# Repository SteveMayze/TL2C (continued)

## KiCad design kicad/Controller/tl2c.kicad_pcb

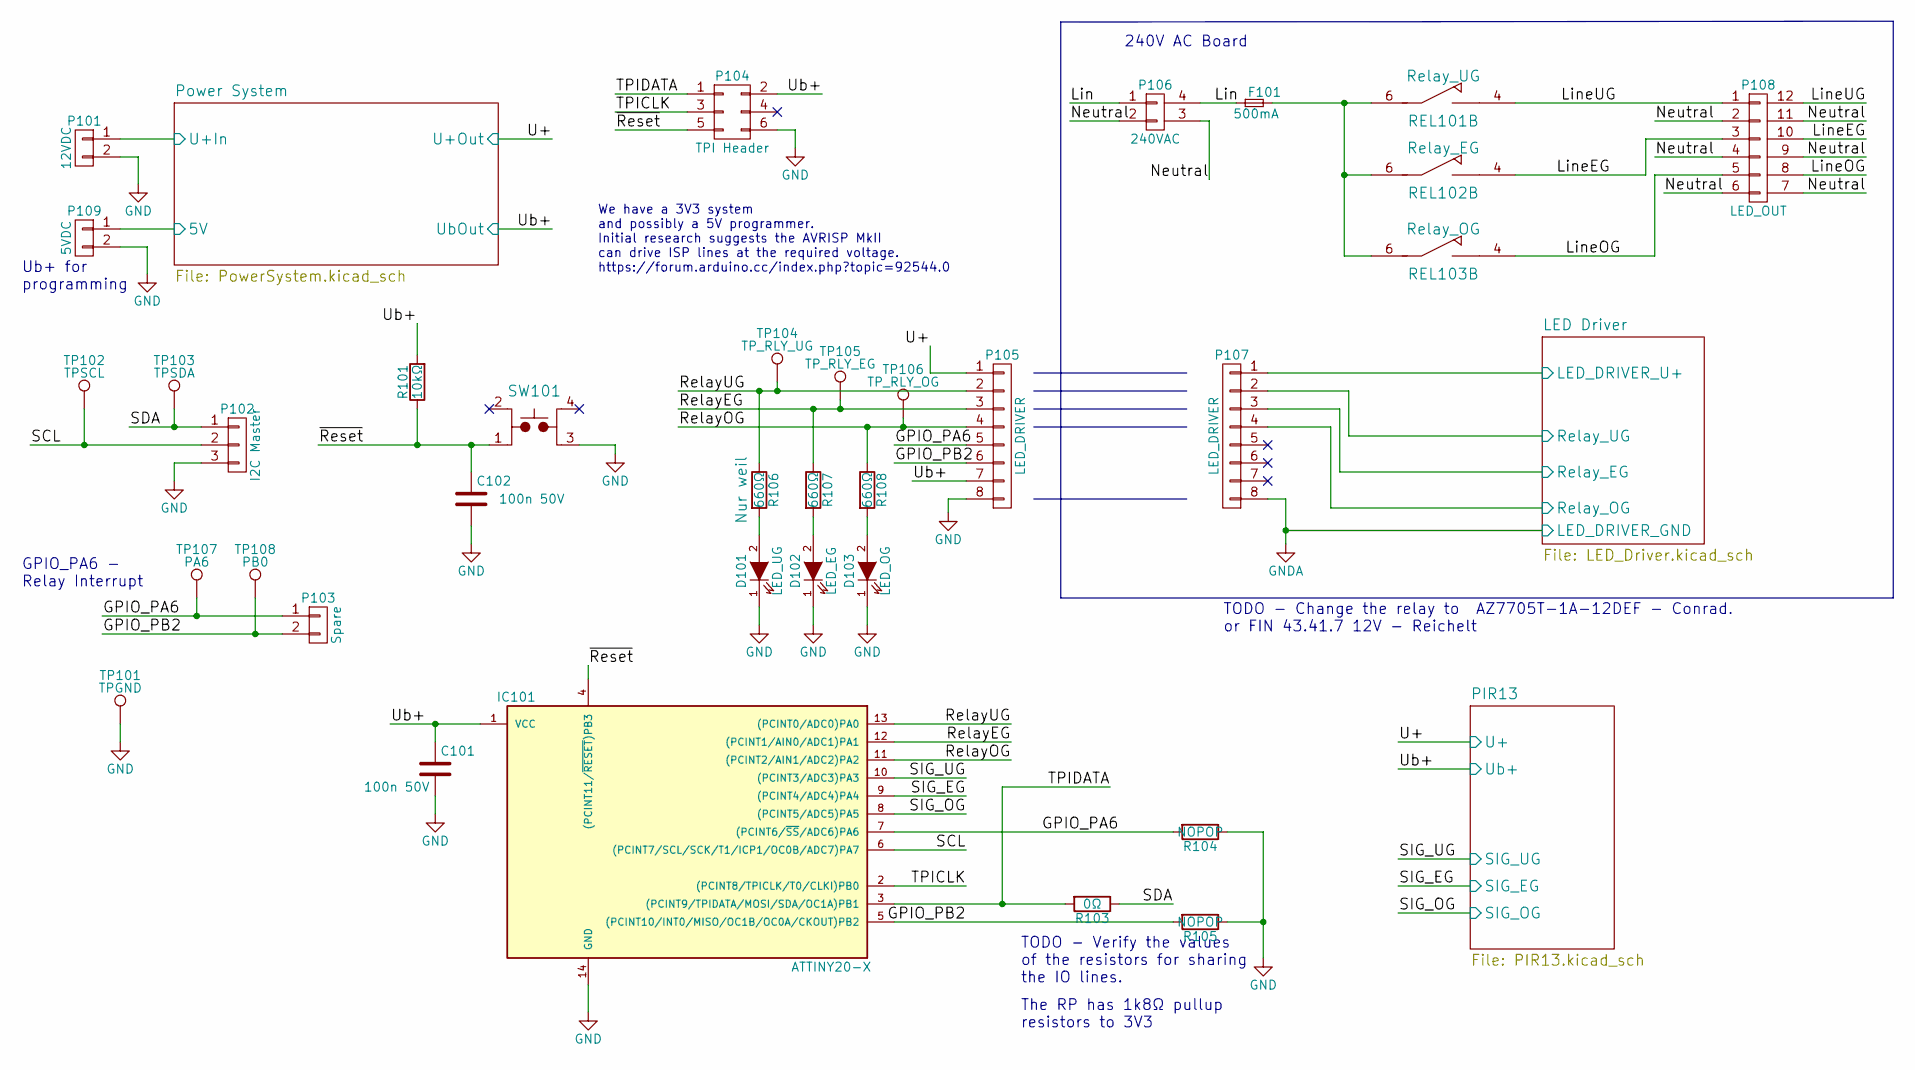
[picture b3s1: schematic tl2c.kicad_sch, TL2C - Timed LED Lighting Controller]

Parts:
C101, C102: 100n 50V; C_0805
D101: LED_UG; LED_0805
D102: LED_EG; LED_0805
D103: LED_OG; LED_0805
F101: 500mA; Fuse_TE5_Littlefuse-ESKA_887_O14; Digikey-PN Value
IC101: ATTINY20-X; SOIC-14_3.9x8.7mm_Pitch1.27mm; Digikey-PN ATTINY20-SSURCT-ND
P101: 12VDC; Pin_Header_Straight_1x02; Digikey-PN Value
P102: I2C Master; Spring_Terminal_Block_1_x_3; Digikey-PN Value
P103: Spare; Pin_Header_Straight_1x02; Digikey-PN Value
P104: TPI Header; TC2030-IDC-FP_ISP_Connector; Digikey-PN Value
P105, P107: LED_DRIVER; Pin_Header_Straight_1x08_Pitch2.54mm; Digikey-PN Value
P106: 240VAC; Spring_Terminal_Block_1_x_2_5mm; Digikey-PN Value
P108: LED_OUT; Spring_Terminal_Block_1_x_6_5mm; Digikey-PN Value
P109: 5VDC; Pin_Header_Straight_1x02_Pitch2.54mm; Digikey-PN Value
R101: 10kΩ; R_0805
R103: 0Ω; R_0805
R104, R105: NOPOP; R_0805
R106, R107, R108: 660Ω; R_0805
REL101: Relay_UG; JW1AFSN-12-F; Digikey-PN Value
REL102: Relay_EG; JW1AFSN-12-F; Digikey-PN Value
REL103: Relay_OG; JW1AFSN-12-F; Digikey-PN Value
SW101: TL3315NF160Q; PTS525SM15SMTR2LFS; Digikey-PN Value
TP101: TPGND; Measurement_Point_Round-SMD-Pad_Small
TP102: TPSCL; Measurement_Point_Round-SMD-Pad_Small
TP103: TPSDA; Measurement_Point_Round-SMD-Pad_Small
TP104: TP_RLY_UG; Measurement_Point_Round-SMD-Pad_Small
TP105: TP_RLY_EG; Measurement_Point_Round-SMD-Pad_Small
TP106: TP_RLY_OG; Measurement_Point_Round-SMD-Pad_Small
TP107: PA6; Measurement_Point_Round-SMD-Pad_Small
TP108: PB0; Measurement_Point_Round-SMD-Pad_Small

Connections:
/GPIO_PA6: IC101.7 ((PCINT6/~SS/ADC6)PA6), P103.1, P105.5, R104.2, TP107.1
/GPIO_PB2: IC101.5 ((PCINT10/INT0/MISO/OC1B/OC0A/CKOUT)PB2), P103.2, P105.6, R105.2, TP108.1
/LED Driver/LED_DRIVER_U+: P107.1; also elsewhere on the board
/LED Driver/Relay_EG: P107.3; also elsewhere on the board
/LED Driver/Relay_OG: P107.4; also elsewhere on the board
/LED Driver/Relay_UG: P107.2; also elsewhere on the board
/Lin: F101.1, P106.1, P106.4
/LineEG: P108.3, P108.10, REL102.4
/LineOG: P108.5, P108.8, REL103.4
/LineUG: P108.1, P108.12, REL101.4
/Neutral: P106.2, P106.3, P108.2, P108.4, P108.6, P108.7, P108.9, P108.11
/PIR13/SIG_EG: IC101.9 ((PCINT4/ADC4)PA4); also elsewhere on the board
/PIR13/SIG_OG: IC101.8 ((PCINT5/ADC5)PA5); also elsewhere on the board
/PIR13/SIG_UG: IC101.10 ((PCINT3/ADC3)PA3); also elsewhere on the board
/PIR13/U+: P105.1; also elsewhere on the board
/PIR13/Ub+: C101.1, IC101.1 (VCC), P104.2, P105.7, R101.2; also elsewhere on the board
/Power System/5V: P109.1; also elsewhere on the board
/Power System/U+In: P101.1; also elsewhere on the board
/RelayEG: IC101.12 ((PCINT1/AIN0/ADC1)PA1), P105.3, R107.1, TP105.1
/RelayOG: IC101.11 ((PCINT2/AIN1/ADC2)PA2), P105.4, R108.1, TP106.1
/RelayUG: IC101.13 ((PCINT0/ADC0)PA0), P105.2, R106.1, TP104.1
/SCL: IC101.6 ((PCINT7/SCL/SCK/T1/ICP1/OC0B/ADC7)PA7), P102.2, TP102.1
/SDA: P102.1, R103.1, TP103.1
/TPICLK: IC101.2 ((PCINT8/TPICLK/T0/CLKI)PB0), P104.3
/TPIDATA: IC101.3 ((PCINT9/TPIDATA/MOSI/SDA/OC1A)PB1), P104.1, R103.2
/~Reset: C102.1, IC101.4 ((PCINT11/~RESET)PB3), P104.5, R101.1, SW101.1
GND: C101.2, C102.2, D101.1 (K), D102.1 (K), D103.1 (K), IC101.14 (GND), P101.2, P102.3, P104.6, P105.8, P109.2, R104.1, R105.1, SW101.3, TP101.1; also elsewhere on the board
GNDA: P107.8; also elsewhere on the board
unnamed: D101.2 (A), R106.2
unnamed: D102.2 (A), R107.2
unnamed: D103.2 (A), R108.2
unnamed: F101.2, REL101.6, REL102.6, REL103.6

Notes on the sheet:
TODO - Verify the values of the resistors for sharing the IO lines.
TODO - Change the relay to AZ7705T-1A-12DEF - Conrad. or FIN 43.41.7 12V - Reichelt
The RP has 1k8Ω pullup resistors to 3V3
GPIO_PA6 - Relay Interrupt
We have a 3V3 system and possibly a 5V programmer. Initial research suggests the AVRISP MkII can drive ISP lines at the required voltage. https://forum.arduino.cc/index.php?topic=92544.0
Ub+ for programming
240V AC Board

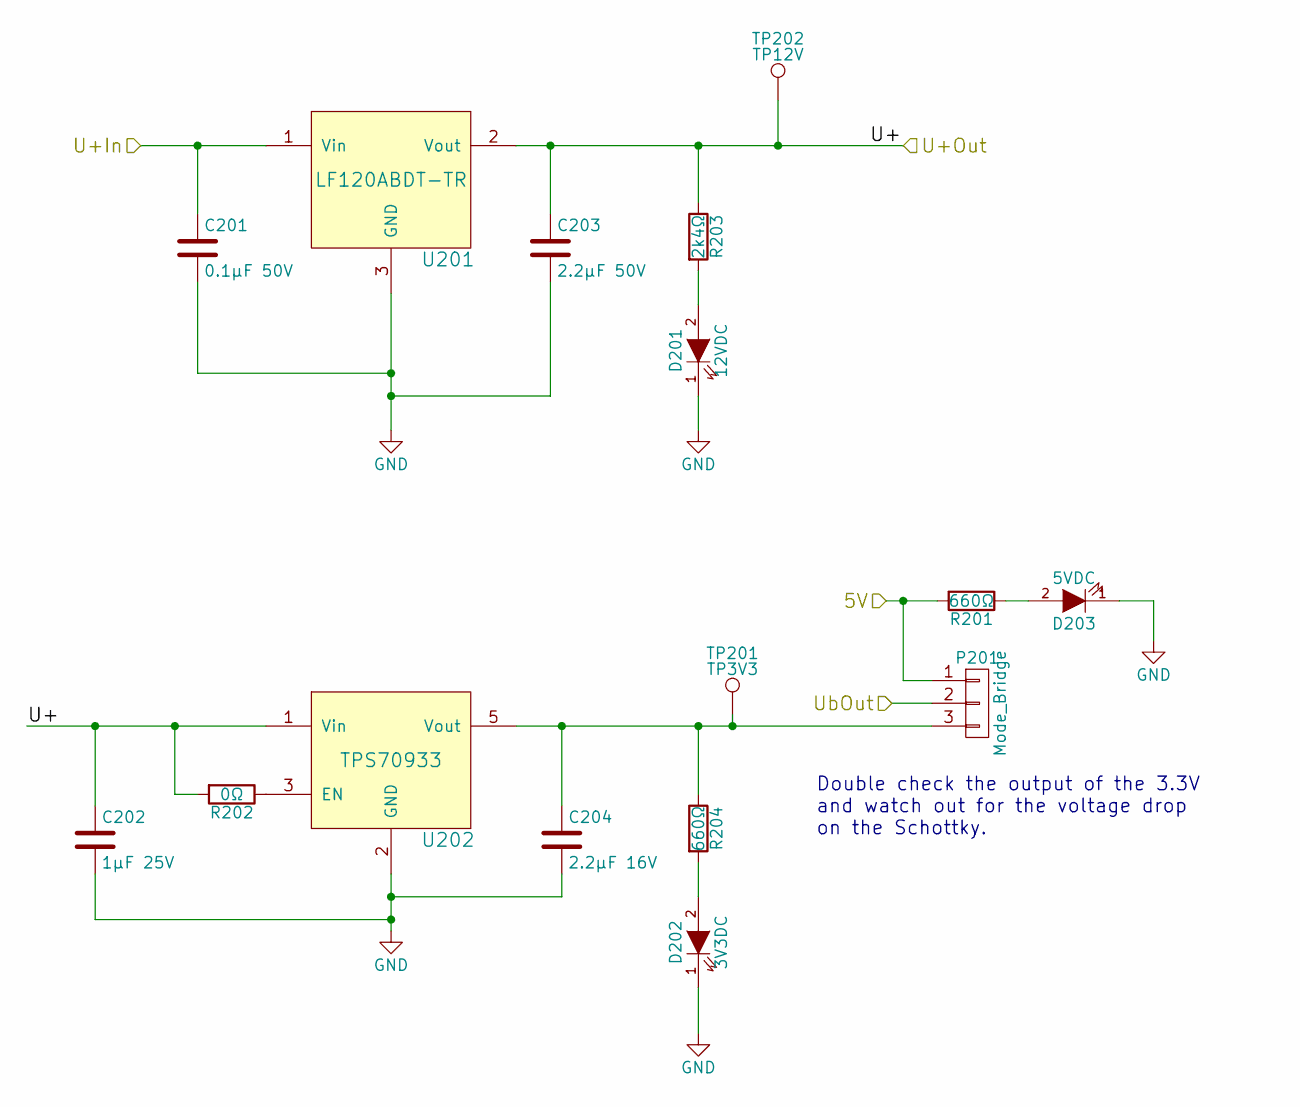
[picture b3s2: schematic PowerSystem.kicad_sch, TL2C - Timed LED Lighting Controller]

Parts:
C201: 0.1μF 50V; C_0805
C202: 1μF 25V; C_1210; Digikey-PN Value
C203: 2.2μF 50V; C_1206; Digikey-PN N/A
C204: 2.2μF 16V; C_1210; Digikey-PN Value
D201: 12VDC; LED_0805
D202: 3V3DC; LED_0805
D203: 5VDC; LED_0805
P201: Mode_Bridge; Pin_Header_Straight_1x03_Pitch2.54mm
R201, R204: 660Ω; R_0805
R202: 0Ω; R_0805
R203: 2k4Ω; R_0805
TP201: TP3V3; Measurement_Point_Round-SMD-Pad_Small
TP202: TP12V; Pin_Header_Straight_1x01; Digikey-PN Value
U201: LF120ABDT-TR; Digikey-PN 497-8330-1-ND
U202: TPS70933; TPS70933DBVR; Digikey-PN 296-35483-1-ND

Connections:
/PIR13/U+: C202.1, C203.1, R202.2, R203.1, TP202.1, U201.2 (Vout), U202.1 (Vin); also elsewhere on the board
/PIR13/Ub+: P201.2; also elsewhere on the board
/Power System/5V: P201.1, R201.2; also elsewhere on the board
/Power System/U+In: C201.1, U201.1 (Vin); also elsewhere on the board
GND: C201.2, C202.2, C203.2, C204.2, D201.1 (K), D202.1 (K), D203.1 (K), U201.3 (GND), U202.2 (GND); also elsewhere on the board
unnamed: C204.1, P201.3, R204.1, TP201.1, U202.5 (Vout)
unnamed: D201.2 (A), R203.2
unnamed: D202.2 (A), R204.2
unnamed: D203.2 (A), R201.1
unnamed: R202.1, U202.3 (EN)

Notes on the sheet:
Double check the output of the 3.3V and watch out for the voltage drop on the Schottky.

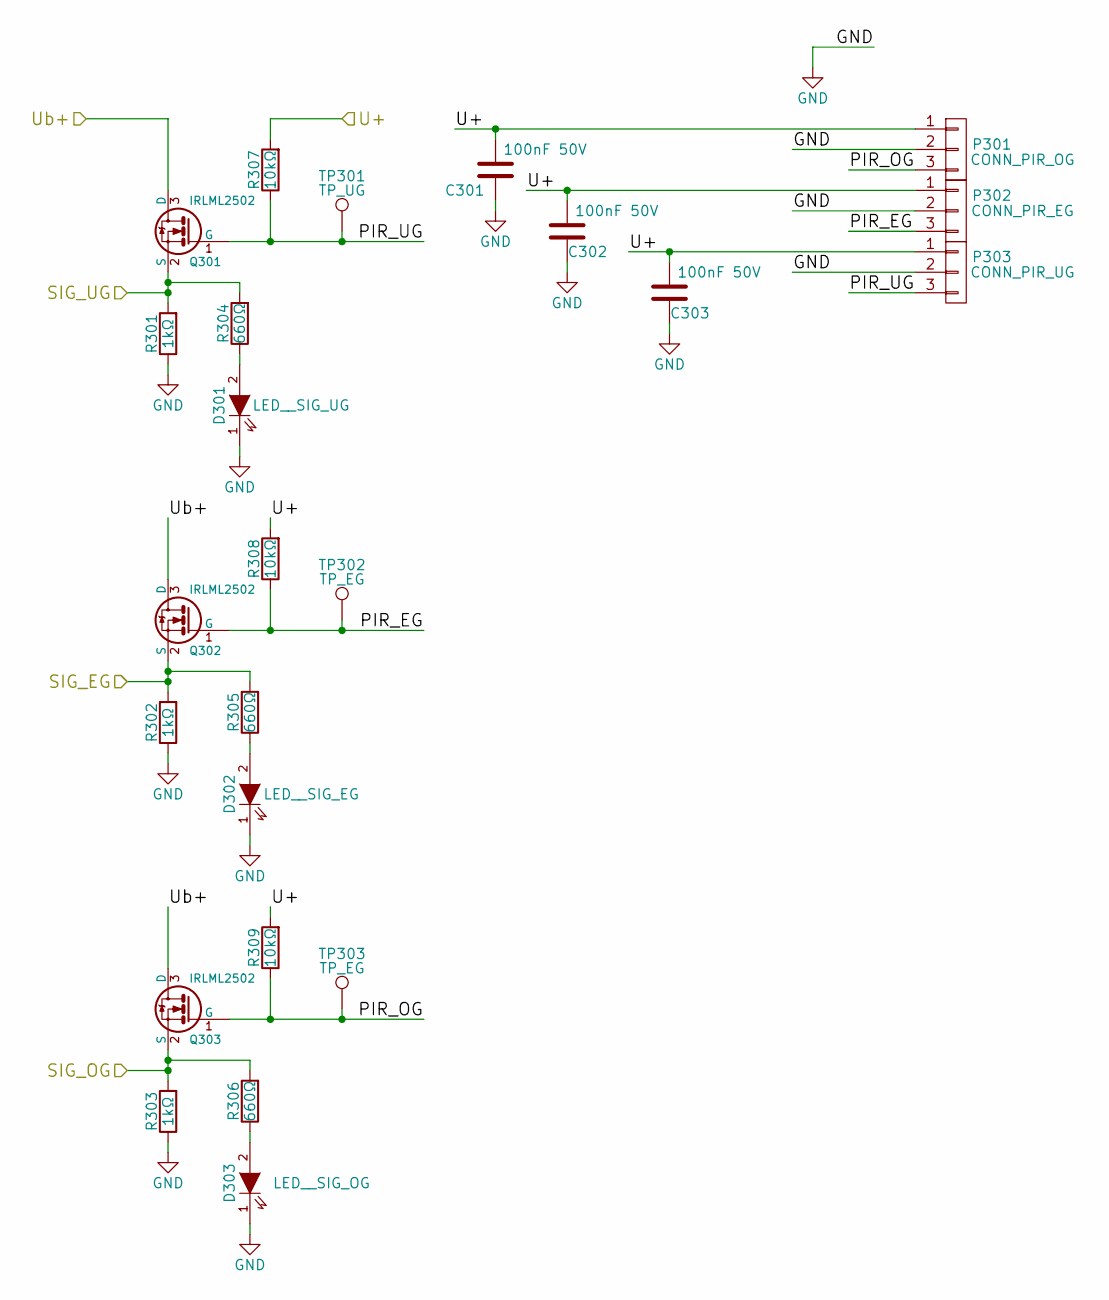
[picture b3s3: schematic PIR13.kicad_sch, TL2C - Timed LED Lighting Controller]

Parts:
C301, C302, C303: 100nF 50V; C_0805
D301: LED__SIG_UG; LED_0805
D302: LED__SIG_EG; LED_0805
D303: LED__SIG_OG; LED_0805
P301: CONN_PIR_OG; Spring_Terminal_Block_1_x_3; Digikey-PN Value
P302: CONN_PIR_EG; Spring_Terminal_Block_1_x_3; Digikey-PN Value
P303: CONN_PIR_UG; Spring_Terminal_Block_1_x_3; Digikey-PN Value
Q301, Q302, Q303: IRLML2502; SOT-23; Digikey-PN IRLML2502GTRPBFCT-ND
R301, R302, R303: 1kΩ; R_0805
R304, R305, R306: 660Ω; R_0805
R307, R308, R309: 10kΩ; R_0805
TP301: TP_UG; Measurement_Point_Round-SMD-Pad_Small
TP302, TP303: TP_EG; Measurement_Point_Round-SMD-Pad_Small

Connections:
/PIR13/PIR_EG: P302.3, Q302.1 (G), R308.1, TP302.1
/PIR13/PIR_OG: P301.3, Q303.1 (G), R309.1, TP303.1
/PIR13/PIR_UG: P303.3, Q301.1 (G), R307.1, TP301.1
/PIR13/SIG_EG: Q302.2 (S), R302.2, R305.2; also elsewhere on the board
/PIR13/SIG_OG: Q303.2 (S), R303.2, R306.2; also elsewhere on the board
/PIR13/SIG_UG: Q301.2 (S), R301.2, R304.2; also elsewhere on the board
/PIR13/U+: C301.2, C302.2, C303.2, P301.1, P302.1, P303.1, R307.2, R308.2, R309.2; also elsewhere on the board
/PIR13/Ub+: Q301.3 (D), Q302.3 (D), Q303.3 (D); also elsewhere on the board
GND: C301.1, C302.1, C303.1, D301.1 (K), D302.1 (K), D303.1 (K), P301.2, P302.2, P303.2, R301.1, R302.1, R303.1; also elsewhere on the board
unnamed: D301.2 (A), R304.1
unnamed: D302.2 (A), R305.1
unnamed: D303.2 (A), R306.1

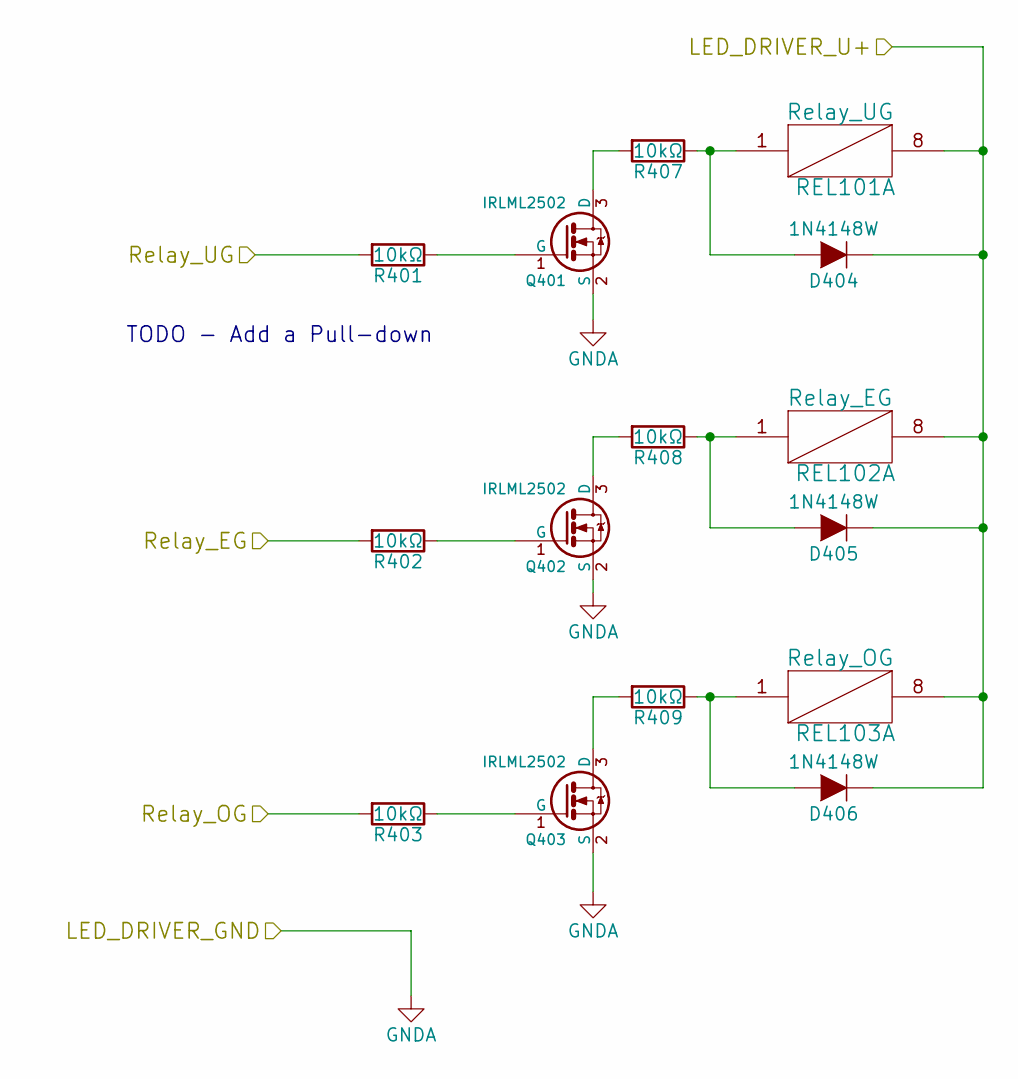
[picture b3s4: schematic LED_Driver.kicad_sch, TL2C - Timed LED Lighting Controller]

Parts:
D404, D405, D406: 1N4148W; SOD-123; Digikey-PN 1N4148W-E3-18CT-ND
Q401: IRLML2502; SOT-23; Digikey-PN IRLML2502GTRPBFCT-ND
Q402, Q403: IRLML2502; SOT-23; Digikey-PN RLML2502GTRPBFCT-ND
R401, R402, R403, R407, R408, R409: 10kΩ; R_0805
REL101: Relay_UG; JW1AFSN-12-F; Digikey-PN N/A
REL102: Relay_EG; JW1AFSN-12-F; Digikey-PN N/A
REL103: Relay_OG; JW1AFSN-12-F; Digikey-PN N/A

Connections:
/LED Driver/LED_DRIVER_U+: D404.1 (K), D405.1 (K), D406.1 (K), REL101.8, REL102.8, REL103.8; also elsewhere on the board
/LED Driver/Relay_EG: R402.2; also elsewhere on the board
/LED Driver/Relay_OG: R403.2; also elsewhere on the board
/LED Driver/Relay_UG: R401.2; also elsewhere on the board
GNDA: Q401.2 (S), Q402.2 (S), Q403.2 (S); also elsewhere on the board
unnamed: D404.2 (A), R407.1, REL101.1
unnamed: D405.2 (A), R408.1, REL102.1
unnamed: D406.2 (A), R409.1, REL103.1
unnamed: Q401.1 (G), R401.1
unnamed: Q401.3 (D), R407.2
unnamed: Q402.1 (G), R402.1
unnamed: Q402.3 (D), R408.2
unnamed: Q403.1 (G), R403.1
unnamed: Q403.3 (D), R409.2

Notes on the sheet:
TODO - Add a Pull-down

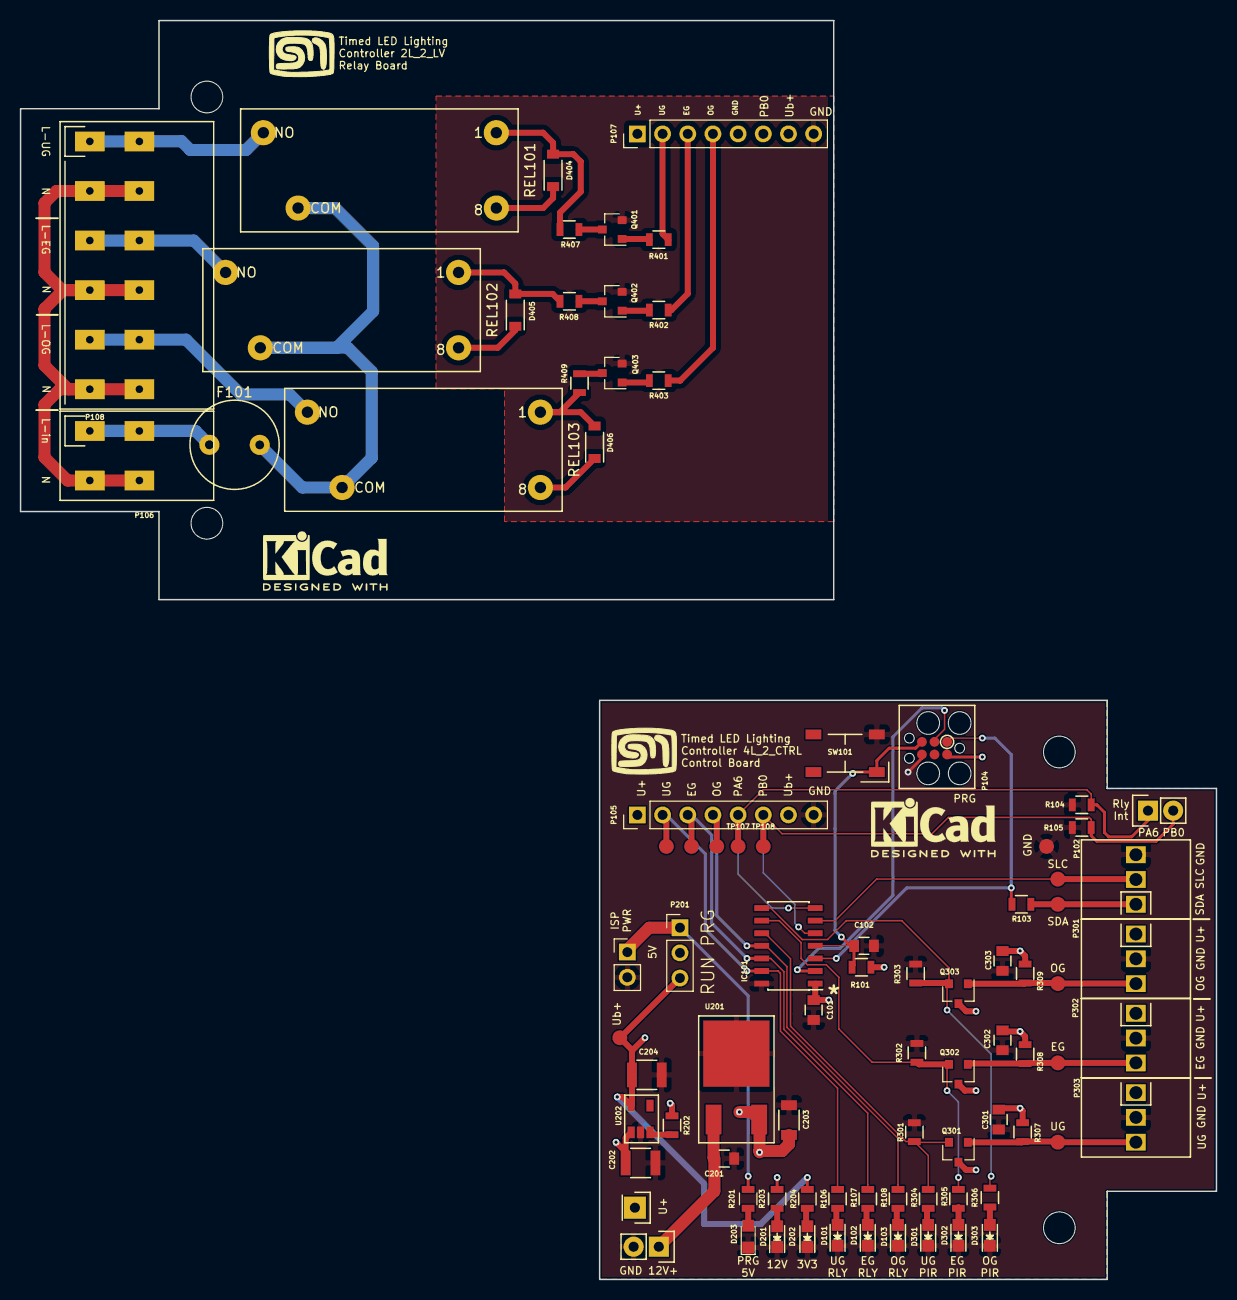
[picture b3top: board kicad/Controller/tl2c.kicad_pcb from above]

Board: 4 copper layers, 120.7 x 127.0 mm, 87 parts (0 on the bottom side), 52 nets.

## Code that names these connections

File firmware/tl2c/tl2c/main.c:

/*
 * tl2c.c
 *
 * Created: 18/02/2017 15:26:52
 * Author : Steve
 */ 

#include <avr/io.h>
#include <avr/interrupt.h>
#include "common.h"
#include "TWI_slave.h"


// volatile unsigned char TL2C_pir_interrupt;
volatile unsigned char timer_delay = 0;
volatile union TL2C_status_reg_t TL2C_pir_state;
unsigned char interrupt_flag;

int main(void)
{
    /* Replace with your application code */

	// Outputs
	// PA0 - UG Untergeschoss relay
	// PA1 - EG	Erdgeschoss relay
	// PA2 - OG	Obergeschoss relay

	// Inputs 
	// PA3 - UG Untergeschoss PIR signal
	// PA4 - EG Erdgeschoss PIR signal
	// PA5 - OG Obergeschoss PIR signal

	// Interrupt (Driver)
	// PA6 - General purpose interrupt output


#define CTC1_MODE	// Testing the timers and interrupts

// The the data direction for the relay outputs
DDRA = 0;
DDRA |= ( 1 << PORTA0 ) | ( 1 << PORTA1 ) | ( 1 << PORTA2 ) | (1 << PORTA6);
PUEA = 0;
PUEA |= ( 1 << PUEA5) | ( 1 << PUEA4) | ( 1 << PUEA3);
// Set the Pin Change interrupts for
PCMSK0 |=   (1<<PCINT5)| (1<<PCINT4)| (1<<PCINT3); // 0b00111000;
GIMSK |= ( 1<<PCIE0 );

#ifdef CTC1_MODE
	// This is the CTC mode whereby the counter registers are are set and a
	// Wave Generator is created. In this example only the OCR0A is used, It
	// is possible also to configure the OCR0B as well.
	// unsigned int startValue = 0x03D0;
	TCCR1A  = 0;										// Reset the operation
	TCCR1B  |=  ( 1 << WGM12 );							// CTC operation
	TCCR1B  |=  ( 5 << CS10  );							// 1024 Pre-scaler
	OCR1AH = 0x03;										// Set the start value - ~0.5Hz
	OCR1AL = 0xD0;										// 16 bit register ... write the high byte first!
	TIMSK |= ( 1 << OCIE1A );							// Enable the interrupt on OCR0A
#endif


#ifdef CTC_MODE
	// This is the CTC mode whereby the counter registers are are set and a
	// Wave Generator is created. In this example only the OCR0A is used, It
	// is possible also to configure the OCR0B as well.
	TCCR0A  = 0;										// Reset the operation
	TCCR0A  |=  ( 1 << WGM01 );							// CTC operation
	TCCR0B  |=  ( 5 << CS00  );							// 1024 Pre-scaler
	OCR0A = 0xF4;									// Set the start value
	TIMSK |= ( 1 << OCIE0A );							// Enable the interrupt on OCR0A
#endif

#ifdef NORMAL_MODE
	// In normal mode, only the TCNT0 needs to be set ( as well as the pre-scaler).
	unsigned int startValue = 0xFF;
	TCCR0A  = 0;										// Reset the operation
	TCCR0B  |=  ( 5 << CS00  );							// 1024 Pre-scaler
	TCNT0  = startValue;								// Set the start value
	TIMSK |= ( 1 << TOIE0 );							// Enable the over flow interrupt
#endif

	PORTA &= ~( 7 << PORTA0 );	// Turn off ALL indicator LEDs.
	led_flag = 0;
	TL2C_Relay_ctl.relay_state.TL2C_INT = 0;
	// TL2C_pir_interrupt = 0;
	TL2C_Registers.TL2C_status_reg.TL2C_PINT = 0;
	TWI_Slave_Initialise( 0x40 );

	TL2C_Relay_ctl.relay1_counter = TL2C_Registers.TL2C_Zone1_On_Delay;
	TL2C_Relay_ctl.relay2_counter = TL2C_Registers.TL2C_Zone2_On_Delay;
	TL2C_Relay_ctl.relay3_counter = TL2C_Registers.TL2C_Zone3_On_Delay;

	sei();

    TWI_Start();
    while (1) 
    {
		// if( TL2C_pir_interrupt ){
		if( TL2C_Registers.TL2C_status_reg.TL2C_PINT ){
			// Here we are confident that there has been a pin change. We have not
			// clarified exactly which pin has changed.

			// If the Zone activate bit is set OR the associated bit in the 
			// status register, then consider this as ON.
			if(TL2C_Registers.TL2C_config_reg.TL2C_Z1A || TL2C_pir_state.TL2C_Z1F ){	// UG - Zone 1
			    TL2C_pir_state.TL2C_Z1F = 0;
			    TL2C_Registers.TL2C_status_reg.TL2C_Z1F = 1;
				TL2C_Relay_ctl.relay_state.TL2C_RLY_UG = 1;
				TL2C_Registers.TL2C_status_reg.TL2C_RINT = 1;
				TL2C_Relay_ctl.relay1_counter = TL2C_Registers.TL2C_Zone1_On_Delay;
			}
			if(TL2C_Registers.TL2C_config_reg.TL2C_Z2A || TL2C_pir_state.TL2C_Z2F){	// EG - Zone 2
			    TL2C_pir_state.TL2C_Z2F = 0;
			    TL2C_Registers.TL2C_status_reg.TL2C_Z2F = 1;
				TL2C_Relay_ctl.relay_state.TL2C_RLY_EG = 1;
				TL2C_Registers.TL2C_status_reg.TL2C_RINT = 1;
				TL2C_Relay_ctl.relay2_counter = TL2C_Registers.TL2C_Zone2_On_Delay;
			}
			if(TL2C_Registers.TL2C_config_reg.TL2C_Z3A || TL2C_pir_state.TL2C_Z3F){	// OG - Zone 3
			    TL2C_pir_state.TL2C_Z3F = 0;
			    TL2C_Registers.TL2C_status_reg.TL2C_Z3F = 1;
				TL2C_Relay_ctl.relay_state.TL2C_RLY_OG = 1;
				TL2C_Registers.TL2C_status_reg.TL2C_RINT = 1;
				TL2C_Relay_ctl.relay3_counter = TL2C_Registers.TL2C_Zone3_On_Delay;
			}
			// TL2C_pir_interrupt = 0;
			TL2C_Registers.TL2C_status_reg.TL2C_PINT = 0;

			// Raise the Interrupt back to the Master
			// TL2C_Registers.TL2C_status_reg.TL2C_RINT = ((TL2C_Relay_ctl.relay_state.TL2C_INT == 0) && (TL2C_Relay_ctl.relay_state.all & 0b00000111));
// 			if (TL2C_Relay_ctl.relay_state.all & 0b00000111) {
// 				TL2C_Registers.TL2C_status_reg.TL2C_RINT = 1;
// 				// TL2C_Relay_ctl.relay_state.TL2C_INT = 1;
// 			}
		}

		// Every pulse cycle...
		if( led_flag){	// The heart beat is used to keep the time for the system.	

			// If the relay is set, then count down.
			if((!TL2C_Registers.TL2C_config_reg.TL2C_Z1A) && TL2C_Relay_ctl.relay_state.TL2C_RLY_UG){
				TL2C_Relay_ctl.relay1_counter--;
				if( !TL2C_Relay_ctl.relay1_counter ){
					TL2C_Relay_ctl.relay_state.TL2C_RLY_UG =  0;
					TL2C_Registers.TL2C_status_reg.TL2C_Z1F = 0;
					TL2C_Registers.TL2C_status_reg.TL2C_RINT = 1;
					TL2C_Relay_ctl.relay1_counter = TL2C_Registers.TL2C_Zone1_On_Delay;
				}
			}

			if((!TL2C_Registers.TL2C_config_reg.TL2C_Z2A) && TL2C_Relay_ctl.relay_state.TL2C_RLY_EG){
				TL2C_Relay_ctl.relay2_counter--;
				if( !TL2C_Relay_ctl.relay2_counter ){
					TL2C_Relay_ctl.relay_state.TL2C_RLY_EG = 0;
					TL2C_Registers.TL2C_status_reg.TL2C_Z2F = 0;
					TL2C_Registers.TL2C_status_reg.TL2C_RINT = 1;
					TL2C_Relay_ctl.relay2_counter = TL2C_Registers.TL2C_Zone2_On_Delay;
				}
			}

			if((!TL2C_Registers.TL2C_config_reg.TL2C_Z3A) && TL2C_Relay_ctl.relay_state.TL2C_RLY_OG){
				TL2C_Relay_ctl.relay3_counter--;
				if( !TL2C_Relay_ctl.relay3_counter ){
					TL2C_Relay_ctl.relay_state.TL2C_RLY_OG = 0;
					TL2C_Registers.TL2C_status_reg.TL2C_Z3F = 0;
					TL2C_Registers.TL2C_status_reg.TL2C_RINT = 1;
					TL2C_Relay_ctl.relay3_counter = TL2C_Registers.TL2C_Zone3_On_Delay;
				}
			}
			
			unsigned char state = PORTA & 0b10111000;
			if( interrupt_flag == 0 && TL2C_Registers.TL2C_status_reg.TL2C_RINT) {
				// Reset the interrupt on the next cycle.
				interrupt_flag = 1;
			} else {
				TL2C_Registers.TL2C_status_reg.TL2C_RINT = 0;
				interrupt_flag = 0;
			}
			TL2C_Relay_ctl.relay_state.TL2C_INT = TL2C_Registers.TL2C_status_reg.TL2C_RINT;
			PORTA = state | TL2C_Relay_ctl.relay_state.all;

// 			if( (led_flag >> red_LED)&1 ){
// 			   PORTA ^= (1 << PORTA0);
// 			}
// 			if( (led_flag >> yellow_LED)&1 ){
// 			   PORTA ^= (1 << PORTA1);
// 			}
// 			if( (led_flag >> green_LED) & 1 ){
// 			   PORTA ^= (1 << PORTA2);
// 			}

			led_flag = 0;
		}
    }
}


ISR(PCINT0_vect){
	// unsigned char enabled = (3>>(TL2C_Registers.TL2C_config_reg.all & 0b00111000));
	// TL2C_Registers.TL2C_status_reg.all = (PINA >> 3) & (TL2C_Registers.TL2C_config_reg.all & 0b00000111);

	// Shift the three input pins three bits to the right
	// Shift the three enable bits four bits to the right
	// AND the result to ensure that all enabled bits are allowed to be registered.
	// TL2C_Registers.TL2C_status_reg.all = (((PINA >> 3) ^ 0xFF) & (TL2C_Registers.TL2C_config_reg.all >> 4));
	TL2C_pir_state.all = (((PINA >> 3) ^ 0xFF) & (TL2C_Registers.TL2C_config_reg.all >> 4));
	TL2C_Registers.TL2C_status_reg.TL2C_PINT = 1;
	// TL2C_pir_interrupt = 1;
}

#ifdef CTC1_MODE
ISR(TIM1_COMPA_vect) {
	// OCR0A = startValue;	// This value does not have to be reset like in Normal Mode.
	led_flag |= (1 << red_LED);
	
}
#endif

#ifdef CTC_MODE
ISR(TIM0_COMPA_vect) {
	// OCR0A = startValue;	// This value does not have to be reset like in Normal Mode.
	// led_flag |= (1 << green_LED);
	// led_flag |= (1 << red_LED);
	timer_delay++;
	if(timer_delay > 3 ){
		led_flag |= (1 << red_LED);
		timer_delay = 0;
	}
	
}
#endif

#ifdef NORMAL_MODE
ISR(TIM0_OVF_vect) {
	TCNT0  = startValue;	// This value must be reset each time to keep the frequency
	//led_flag |= (1 << red_LED);
}
#endif

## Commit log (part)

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2016-12-10 Initial project comments.
2016-12-10 Title for the intro
2016-12-10 Corrected title
2016-12-10 Initial checkin of the project structure
2016-12-10 Started the schematic
2016-12-10 Completed the initial schematic
2016-12-11 Added some data sheets to track
2016-12-14 Changes to the schematic after a review - added further test points and LEDs
2016-12-16 Started assigning foot prints to the parts
2016-12-17 Added more footprints to the parts
2016-12-17 Provided a place holder connector for the 240V side and started the layout
2016-12-18 Added the diode datasheet
2016-12-18 Started adding tracks to the layout
2016-12-18 Retried the track layouts for the contoller part.
2016-12-20 Completed the first draft of the board - moved to 4 layers
2016-12-23 A change of heart with some of the parts due to sourcing
2016-12-23 Some part changes due to sourcing
2016-12-23 Split the board to two separate boards one 2layer the other 4layer
2016-12-24 Revamped the master pcb layout for the mounting holes and the actual footprint for the terminal blocks
2016-12-26 Fixed junction on three wires instead of two, two wire connections. Added first look at the Gerbers
2016-12-26 Corrected the Ub+ to the LV board... should be U+
2016-12-29 The intial re-hash of the layout for the selected case
2016-12-30 More rework on the board for the correct terminal blocks and case
2016-12-31 More layout re-work and footprint changes
2016-12-31 Finished off the refactoring for the housing and terminal blocks
2017-01-02 Included a small fuse on the Active. Finalised the board
2017-01-02 Added the Reichelt-PN to the fuse for the last commit
2017-01-05 Finilised the layout with a larger pin header to expose spare pins to relay driver board
2017-01-05 Created the Gerbers and submitted the order for boards and stensils
2017-01-27 Updated the footprint for the relay - larger holes
2017-02-04 Altered the fuse footprint to accomdate the fulse holder instead of the part
2017-02-17 Fixed some issues with the schematic and layout
2017-02-17 Started the firmware and added the Atmel examples for now
2017-02-17 Added the changes to the .gitignore for the firmware
2017-02-19 Back to Blinky - implemented bliker with interrupts as a starter
2017-03-03 Added the a POC assembly version of the driver
2017-03-03 TWI in assembly - a base sample to work from
2017-03-03 The C Project for researching TWI Just on hold for the moment
2017-03-12 C alorithim is now working as a base model
2017-03-21 Working example of writing to and reading from the 6 registers
2017-03-23 The first full working model of the firmware
2017-03-25 A fully working version under the ELV test harness
2017-03-25 Added the data-sheet for the project
2017-03-27 Made a correction to a net label
2017-03-28 Updated the data-sheet to change of the usage of register 0x05
2017-03-30 Finalised the corrections to the board
2017-04-22 Corrected the label on the ISP Power connector
2017-04-25 Finalised the layout/footprint changes for the 240V board
2017-04-29 Corrected an issue with the status register
2017-04-29 Updated the datasheet and added the connection diagram
2017-04-30 Updated the data-sheet for some small corrections
2017-04-30 Updated the data-sheet for some small corrections... again
2017-04-30 Updated the data-sheet for some small corrections... and again
2017-05-02 Published the PDF version of the data sheet
2017-05-03 Corrections to the default address comment in the datasheet
2017-05-11 Cleaned the code up a little
2017-05-11 Initial version for enabling the interrupt to the master
2017-05-11 Updated the datasheet to include the interrupt flag in the status register
2017-05-16 Corrected some small issues with the interrupt signalling
2017-05-21 Set the interrupt as a one second pulse rather than continuous
2017-05-30 Created some images/icons for the UI
2017-05-30 Data sheet changes
2017-06-19 Started the Rpi Adapter
2017-06-19 Layout done and 2L_1 is sent to OSH Park
2017-06-20 Set the Rx and Tx resistors together incase of swapping
2017-07-06 Small changes to the clearances
2017-07-16 Started Hutschiene design
2017-07-16 Continuing with the Hutschiene design and layout
2017-07-17 Further work on the redesign
2017-07-19 Further work on the new Hutschiene Layout
2017-07-19 Further to the layout for the Hutschiene
2017-07-19 Hutschiene layout intermediate save
2017-07-23 Created a new KiCad Logo and updated the gitigore for .DS_Store
2017-07-23 Completed draft of hutshiene layout
2017-07-24 Reworked the layout for the CamdenBoss enclosure
2017-07-24 Adjusted the size and location of the terminal blocks
2017-07-31 Final adjustments for the seperation and push to OSH Park
2017-07-31 Pushed the boards to OSHPark
2017-08-02 Corrections to the terminal block drill holes
2017-08-08 Re-worked the RPi Adapter to be more compact.
2017-08-19 Reworked the RPi Adapter 2L_4 for RJ45
2017-08-20 Flipped the RJ45 to the bottom
2017-08-23 Flipped the programming head to the bottom
2017-08-26 Flipped the programming header to the bottom (correct layout)
2017-08-26 Flipped the programming header properly
2017-08-26 Fixed some labels and text
2017-08-30 Correction to the board connected and seperated out the pwr
2017-09-13 More refinements based on the DIN prototype tests
2017-09-17 Enhancements to the RPi Adapter and DIN boards
2017-09-18 In preperation for using a stencil - moved most 0805 back from handsolder to normal
2017-10-05 Corrected issues with the connectors - Pushing to OSH Park
2017-10-05 Created the stensil archive
2017-10-17 Added the datasheet for the stairwell LEDs
2017-10-17 Commiting the gerbers for the Rpi RJ45 adapter
2017-10-30 Moved the RJ45 for the back-plane placement
2017-11-26 Reduced the size of the Rpi_Adapter to make a better fit into the enclosure
2017-11-27 Radically reduced the size of the board
2019-04-16 Upgrade to KiCad 5.1
2024-02-06 Bringing the board into the latest KiCad
2024-02-10 First draft of the esp32 module
2024-02-11 Created the front panel artwork with drill marks
2024-02-11 Updated the PDFs
2024-02-11 Added some comments
2024-02-18 Pin reassignments after starting the firmware
2024-03-09 Completed the release for OSH Park
2024-03-10 Created rev 1.01 - Addes some more labels and annotations
2024-04-16 Reseated the RJ45
2024-04-21 Doc update
2024-05-05 R1 correction
2024-05-24 Adding some documentation
2024-06-29 Added some doc
2024-06-29 changes to help with the writeup
2024-06-30 Updated the artwork and documentation
2024-07-01 Esp32 (#1)
    * First draft of the esp32 module
    * Created the front panel artwork with drill marks
    * Updated the PDFs
    * Added some comments
    * Pin reassignments after starting the firmware
    * Completed the release for OSH Park
